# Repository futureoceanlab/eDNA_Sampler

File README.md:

# eDNA Sampler
This is a project that controls an autonomous eDNA Sampler. There are two modules: ESP8266 based hardware controller and a Django Web Application for interact with ESP8266 wirelessly.

The detailed documentation on architecture, how-to-build, apparatus and testing can be found in eDNA_sampler.pdf in this repository. Furthermore, the link to view the overleaf can be found [here](https://www.overleaf.com/read/nvktmdfzfmym). Please send an email to junsuj@mit.edu if you would like to edit the documentation. 

## Current Apparatus
Feb 2020: We currently have one full-system ready to be disassembled in the lab. We have four packs of batteries and three housings with connectors ready to be assemebled. We have 9 PCB boards and required components to be soldered on the PCB.

# Overview of this repository

## webapp: Web App for online deployment configuration / data retrieval
The program is run on a virtual environment, so install the virtualenv on the machine that will run the Web App.

```bash
pip3 install virtualenv
```

In case that the virtualenv is installed in a path that is not listed (i.e. virtualenv will complain saying that there is no such command), please add the following line to the end of ~/.profile 

```bash
PATH=$PATH:$HOME/.local/bin
```

in eDNA_Sampler/webapp, enter the following line in the terminal

```bash
virtualenv env
source env/bin/activate
``` 

This should activate the virtual environment, and you are ready to install the required packages

```bash
pip3 install -r requirements.txt
```

The webserver hosts' IP address can be found at WLAN0 interface by running the following:

```bash
ifconfig
```

In the webapp directory, run the server

```bash
python3 manage.py runserver 0.0.0.0:5000
```

0.0.0.0 will listen to other devices connected through every interfaces. 5000 is the port, and it can be different as long as it does not coincide with other used ports. 

Finally, check the Firewall if the client cannot access the webapp.

## sampler_mcu: ESP8266 Based Arduino code
The system uses ESP8266 Huzzah from Adafruit and a variety of libraries, and thus, Arduino IDE requires some setup.

In particular, the libraries that need to be installed are:
[ESP8266](https://learn.adafruit.com/adafruit-huzzah-esp8266-breakout/using-arduino-ide), 
[GrooveNfc](https://github.com/Seeed-Studio/Seeed_Arduino_NFC), 
ArduinoJson,
[MS5837](https://github.com/bluerobotics/BlueRobotics_MS5837_Library), 
[TSYS01](https://github.com/bluerobotics/BlueRobotics_TSYS01_Library).

[ESP8266 Huzzah](https://learn.adafruit.com/adafruit-huzzah-esp8266-breakout/using-arduino-ide) explains how to program the device using FTDI converter.

## mechanical
This directory contains designs and schematics for mechanical components of the eDNA Sampler.
Specifically, we have 3D design of the battery housing and acrylic plates for the pvc clamp shell. 
There is also the electronics housing drawing for machining.

## pcb
This is the schematic and layout of the PCB design of the electronics.

## archive
This is a folder with ancient codes and files that were onced developed. They are irrelevant at this point, but archived in this folder.

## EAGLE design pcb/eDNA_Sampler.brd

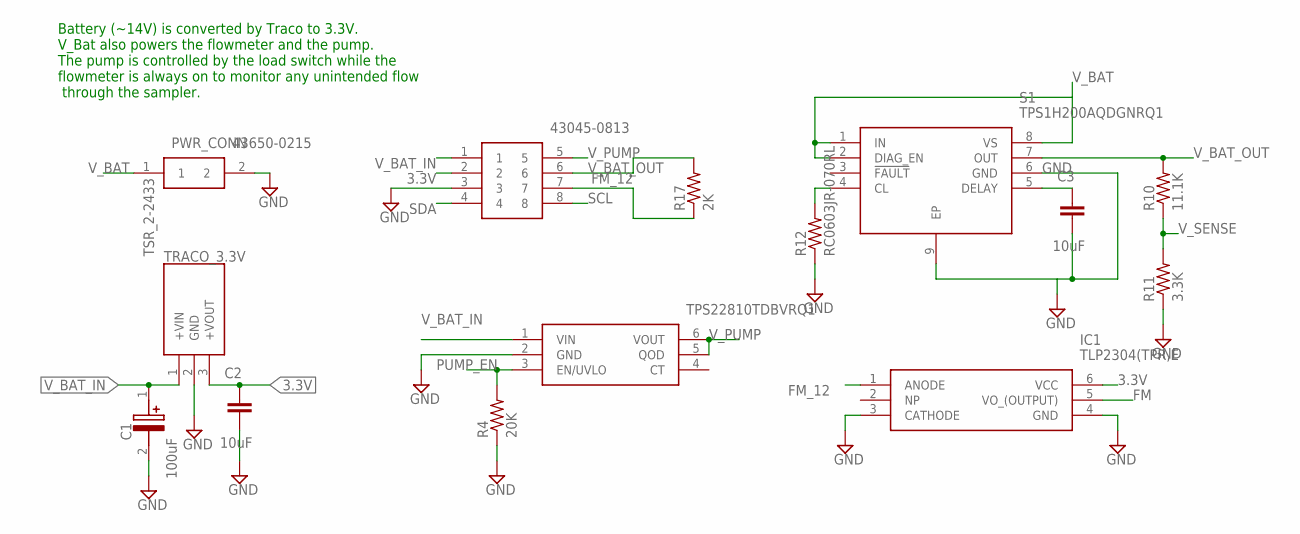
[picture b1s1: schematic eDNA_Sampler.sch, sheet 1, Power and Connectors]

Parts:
C1: 100uF; CAPPRD250W50D680H1250
C2, C3: 10uF; CAP_0603
IC1: TLP2304(TPR,E; SOIC127P700X230-6N
LOAD_SWITCH: TPS22810TDBVRQ1; SOT95P280X145-6N
PENETRATOR_CONN: 43045-0813
PWR_CONN: 43650-0215; 43650-0217
R4: 20K; RES_0603
R10: 11.1K; RES_0603
R11: 3.3K; RES_0603
R12: RC0603JR-070RL; RES_0603
R17: 2K; RES_0603
S1: TPS1H200AQDGNRQ1; SOP65P490X110-9N
TRACO_3.3V: TSR_2-2433; TSR-2

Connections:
3.3V: C2.1, IC1.6 (VCC), PENETRATOR_CONN.2, TRACO_3.3V.3 (+VOUT); also elsewhere on the board
FM: IC1.5 (VO_(OUTPUT)); also elsewhere on the board
FM_12: IC1.1 (ANODE), PENETRATOR_CONN.7, R17.1
GND: C1.2 (-), C2.2, C3.2, IC1.3 (CATHODE), IC1.4 (GND), LOAD_SWITCH.2 (GND), PENETRATOR_CONN.3, PWR_CONN.2, R4.1, R11.1, R12.1, S1.6 (GND), S1.9 (EP), TRACO_3.3V.2 (GND); also elsewhere on the board
unnamed: R12.2, S1.4 (CL)
unnamed: C3.1, S1.5 (DELAY)
PUMP_EN: LOAD_SWITCH.3 (EN/UVLO), R4.2; also elsewhere on the board
SCL: PENETRATOR_CONN.8; also elsewhere on the board
SDA: PENETRATOR_CONN.4; also elsewhere on the board
V_BAT: PWR_CONN.1, S1.1 (IN), S1.2 (DIAG_EN), S1.8 (VS)
V_BAT_IN: C1.1 (+), LOAD_SWITCH.1 (VIN), PENETRATOR_CONN.1, TRACO_3.3V.1 (+VIN)
V_BAT_OUT: PENETRATOR_CONN.6, R10.2, R17.2, S1.7 (OUT)
V_PUMP: LOAD_SWITCH.5 (QOD), LOAD_SWITCH.6 (VOUT), PENETRATOR_CONN.5
V_SENSE: R10.1, R11.2; also elsewhere on the board

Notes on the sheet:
Battery (~14V) is converted by Traco to 3.3V. V_Bat also powers the flowmeter and the pump. The pump is controlled by the load switch while the flowmeter is always on to monitor any unintended flow through the sampler.

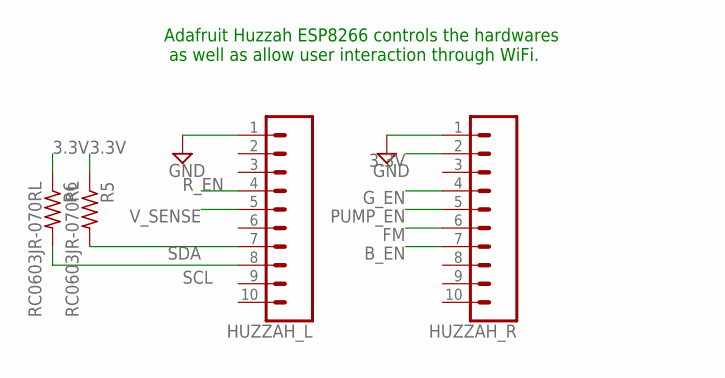
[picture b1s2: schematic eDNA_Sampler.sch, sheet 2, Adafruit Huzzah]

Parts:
HUZZAH_L: CONN_10"; 1X10
HUZZAH_R: CONN_10"; 1X10
R5, R6: RC0603JR-070RL; RES_0603

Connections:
3.3V: HUZZAH_R.2, R5.1, R6.1; also elsewhere on the board
B_EN: HUZZAH_R.7; also elsewhere on the board
FM: HUZZAH_R.6; also elsewhere on the board
GND: HUZZAH_L.1, HUZZAH_R.1; also elsewhere on the board
G_EN: HUZZAH_R.4; also elsewhere on the board
PUMP_EN: HUZZAH_R.5; also elsewhere on the board
R_EN: HUZZAH_L.4; also elsewhere on the board
SCL: HUZZAH_L.8, R6.2; also elsewhere on the board
SDA: HUZZAH_L.7, R5.2; also elsewhere on the board
V_SENSE: HUZZAH_L.5; also elsewhere on the board

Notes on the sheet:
Adafruit Huzzah ESP8266 controls the hardwares as well as allow user interaction through WiFi.

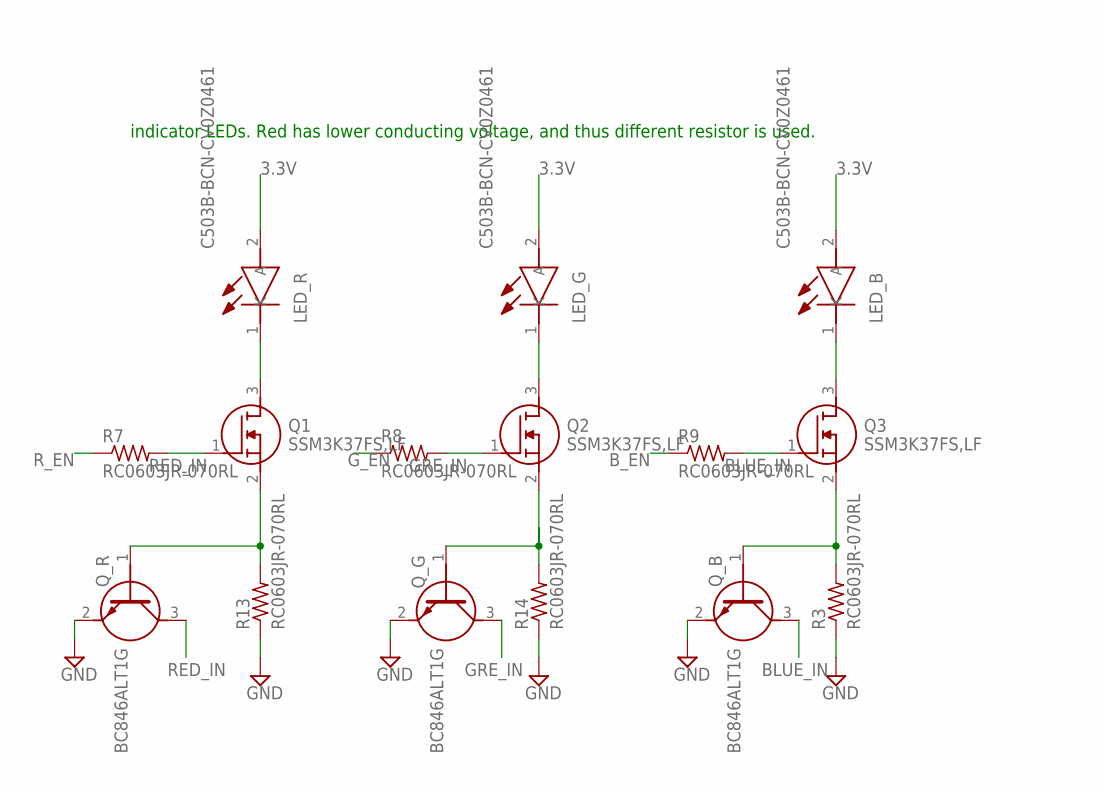
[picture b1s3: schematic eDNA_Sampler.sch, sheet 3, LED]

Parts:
LED_B: C503B-BCN-CV0Z0461; C503B-BCN
LED_G: C503B-BCN-CV0Z0461; C503B-BCN
LED_R: C503B-BCN-CV0Z0461; C503B-BCN
Q1, Q2, Q3: SSM3K37FS,LF; SSM3K37FSLF
Q_B: BC846ALT1G; SOT95P237X111-3N
Q_G: BC846ALT1G; SOT95P237X111-3N
Q_R: BC846ALT1G; SOT95P237X111-3N
R3, R7, R8, R9, R13, R14: RC0603JR-070RL; RES_0603

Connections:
3.3V: LED_B.2 (A), LED_G.2 (A), LED_R.2 (A); also elsewhere on the board
BLUE_IN: Q3.1 (G), Q_B.3 (C), R9.2
B_EN: R9.1; also elsewhere on the board
GND: Q_B.2 (E), Q_G.2 (E), Q_R.2 (E), R3.1, R13.1, R14.1; also elsewhere on the board
GRE_IN: Q2.1 (G), Q_G.3 (C), R8.2
G_EN: R8.1; also elsewhere on the board
unnamed: LED_R.1 (K), Q1.3 (D)
unnamed: LED_G.1 (K), Q2.3 (D)
unnamed: Q2.2 (S), Q_G.1 (B), R14.2
unnamed: Q1.2 (S), Q_R.1 (B), R13.2
unnamed: Q3.2 (S), Q_B.1 (B), R3.2
unnamed: LED_B.1 (K), Q3.3 (D)
RED_IN: Q1.1 (G), Q_R.3 (C), R7.2
R_EN: R7.1; also elsewhere on the board

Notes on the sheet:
indicator LEDs. Red has lower conducting voltage, and thus different resistor is used.

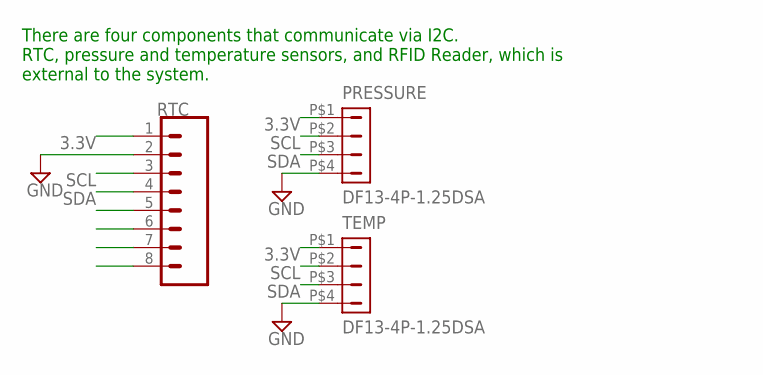
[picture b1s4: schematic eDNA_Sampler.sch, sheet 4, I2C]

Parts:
PRESSURE: DF13-4P-1.25DSA
RTC: CONN_08"; 1X08
TEMP: DF13-4P-1.25DSA

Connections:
3.3V: PRESSURE.P$1 (1), RTC.1, TEMP.P$1 (1); also elsewhere on the board
GND: PRESSURE.P$4 (4), RTC.2, TEMP.P$4 (4); also elsewhere on the board
SCL: PRESSURE.P$2 (2), RTC.3, TEMP.P$2 (2); also elsewhere on the board
SDA: PRESSURE.P$3 (3), RTC.4, TEMP.P$3 (3); also elsewhere on the board

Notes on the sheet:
There are four components that communicate via I2C. RTC, pressure and temperature sensors, and RFID Reader, which is external to the system.

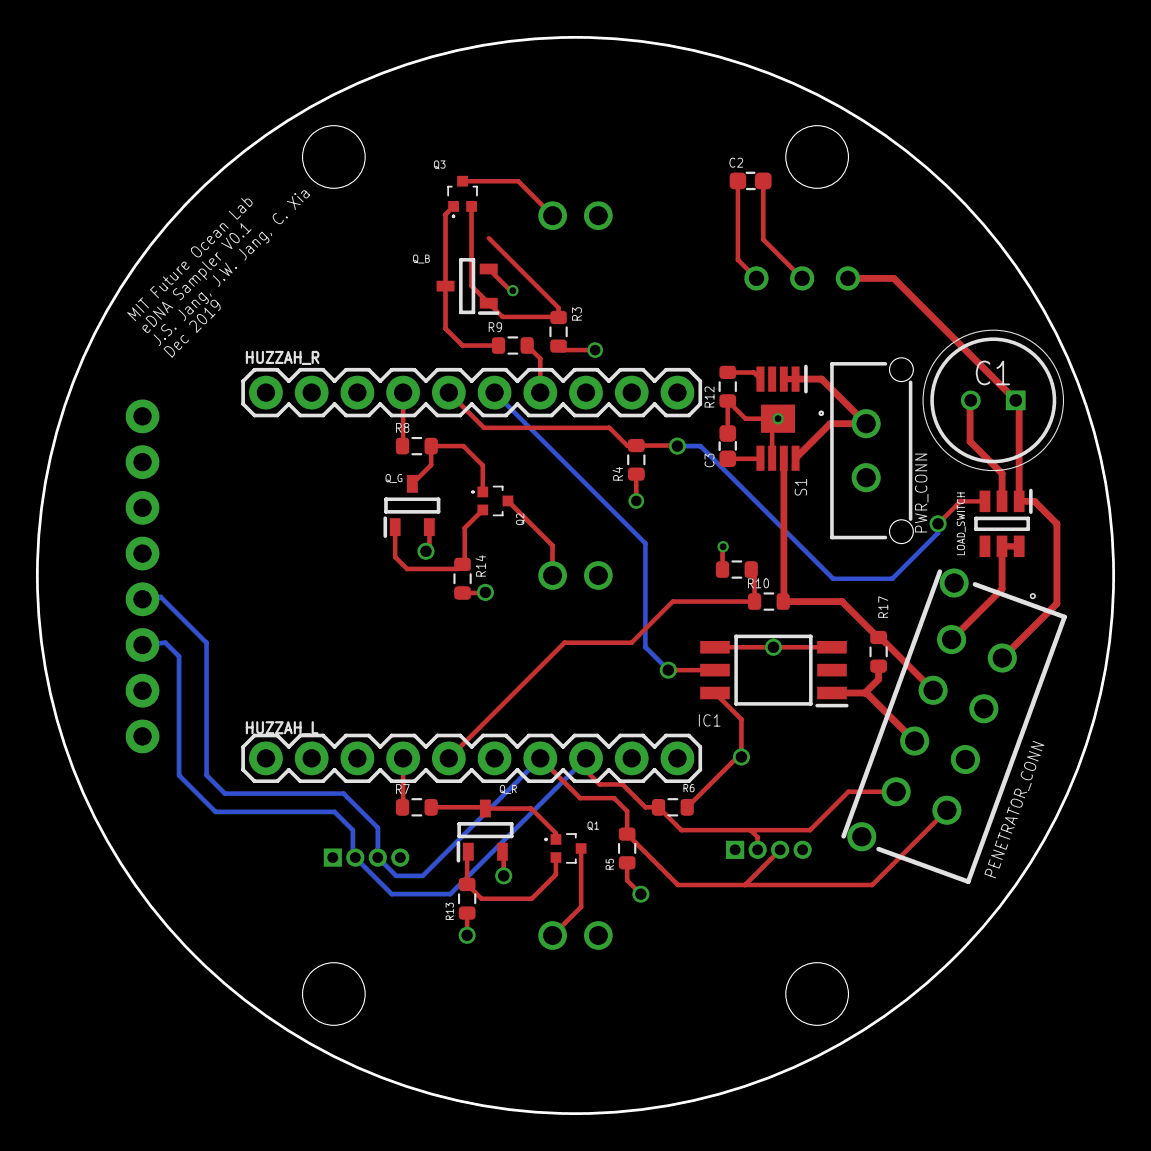
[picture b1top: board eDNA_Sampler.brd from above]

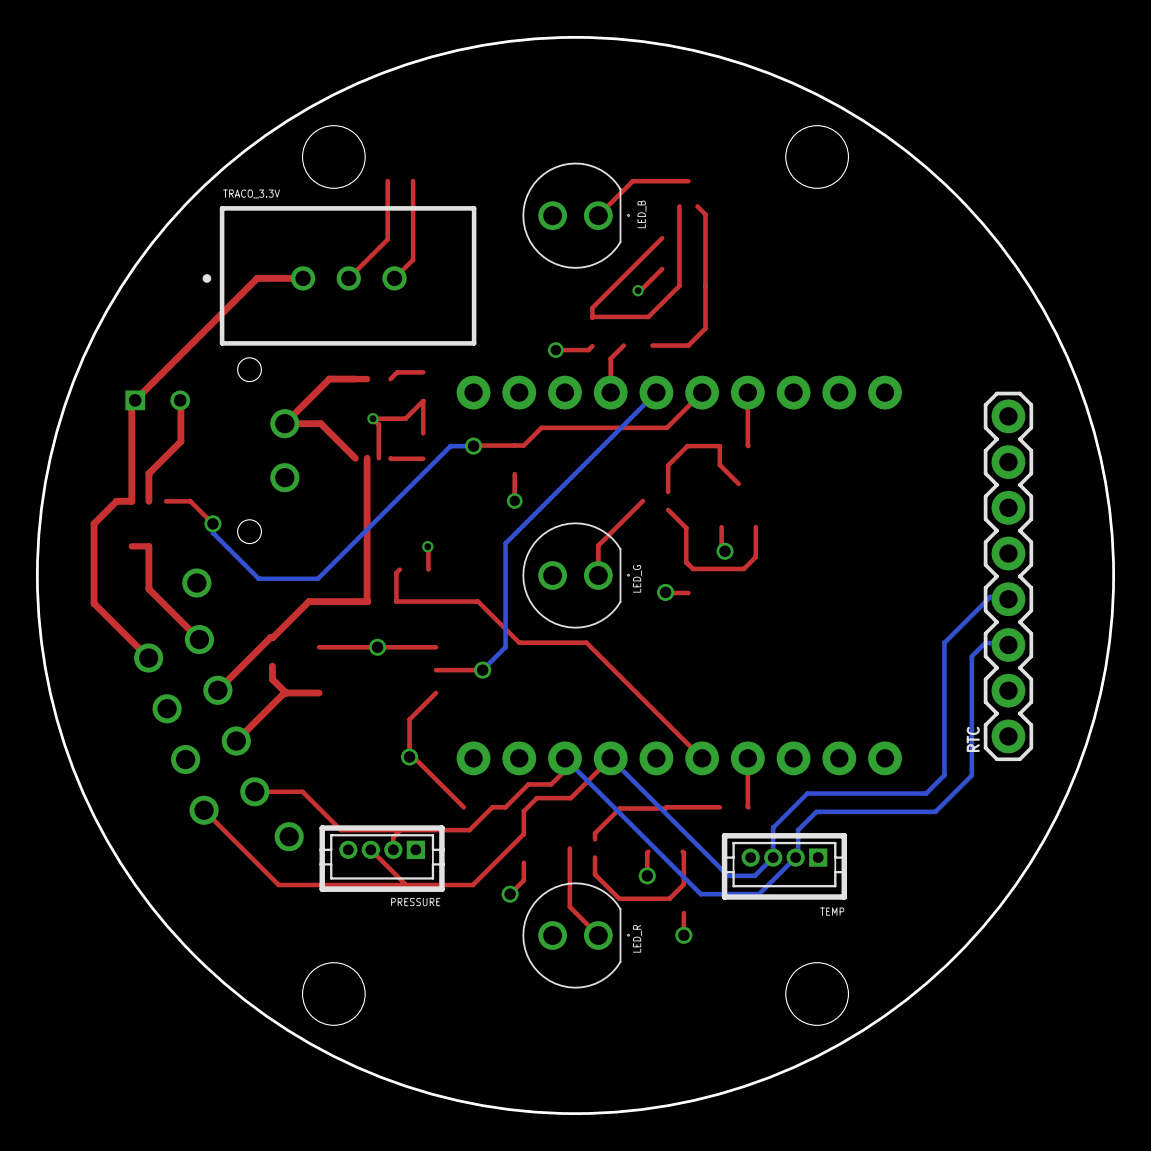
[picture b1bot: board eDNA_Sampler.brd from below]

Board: 4 copper layers, 59.8 x 59.8 mm, 36 parts (7 on the bottom side), 26 nets.

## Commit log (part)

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2019-11-05 add flowmeter tick conversion
2019-11-05 add a script that will automatically run the server with virtualenv
2019-11-06 uncomment the conditions on deployment
2019-11-06 add ifdef DEBUG clauses
2019-11-06 change the name of the file to match the directory name
2019-11-07 cater to the new loggistics where the RFID will be tagged and power cycled
2019-11-09 added library for kellerLP
2019-11-21 changes to satisfy the depth trigger
2019-11-30 changes to adapt more parameters
2019-11-30 modularize the conditionals
2019-12-02 log files and conditions update
2019-12-02 receives log file, checkes for invalid inputs
2019-12-03 incorrect formatted data file and log conditions
2019-12-03 added instruction for details page
2019-12-03 user manual added
2019-12-04 modified templates to work with smaller screens
2019-12-04 add non-empty log file
2019-12-04 update readme file
2019-12-07 add plot creation to webapp
2019-12-07 requirement update with matplot
2019-12-07 Bump django from 2.2.6 to 2.2.8 in /webapp
    Bumps [django](https://github.com/django/django) from 2.2.6 to 2.2.8.
    - [Release notes](https://github.com/django/django/releases)
    - [Commits](https://github.com/django/django/compare/2.2.6...2.2.8)
2019-12-08 hardcoded version
2020-01-14 update webapp fix with plots and offline code
2020-01-14 remove DS Store
2020-01-23 add battery, housing and pvc shell .step files as well as drawings
2020-01-23 add circuit schematics and layouts
2020-01-23 refactor the code into a sampler_mcu directory
2020-01-23 remove environment files
2020-01-23 remove eDNA_v0
2020-01-23 move offline code to archive
2020-01-23 remove DS store file
2020-01-23 add data and logs directory to webapp
2020-01-23 remove pycache in migrations
2020-01-23 added comments with details on each functions
2020-01-23 update the readme
2020-01-23 update django framework
2020-01-23 Bump twisted from 17.9.0 to 19.7.0 in /webapp
    Bumps [twisted](https://github.com/twisted/twisted) from 17.9.0 to 19.7.0.
    - [Release notes](https://github.com/twisted/twisted/releases)
    - [Changelog](https://github.com/twisted/twisted/blob/trunk/NEWS.rst)
    - [Commits](https://github.com/twisted/twisted/compare/twisted-17.9.0...twisted-19.7.0)
2020-01-23 Bump pyyaml from 3.12 to 5.1 in /webapp
    Bumps [pyyaml](https://github.com/yaml/pyyaml) from 3.12 to 5.1.
    - [Release notes](https://github.com/yaml/pyyaml/releases)
    - [Changelog](https://github.com/yaml/pyyaml/blob/master/CHANGES)
    - [Commits](https://github.com/yaml/pyyaml/compare/3.12...5.1)
2020-01-23 Bump cryptography from 2.1.4 to 2.3 in /webapp
    Bumps [cryptography](https://github.com/pyca/cryptography) from 2.1.4 to 2.3.
    - [Release notes](https://github.com/pyca/cryptography/releases)
    - [Changelog](https://github.com/pyca/cryptography/blob/master/CHANGELOG.rst)
    - [Commits](https://github.com/pyca/cryptography/compare/2.1.4...2.3)
2020-01-23 Bump requests from 2.18.4 to 2.20.0 in /webapp
    Bumps [requests](https://github.com/requests/requests) from 2.18.4 to 2.20.0.
    - [Release notes](https://github.com/requests/requests/releases)
    - [Changelog](https://github.com/psf/requests/blob/master/HISTORY.md)
    - [Commits](https://github.com/requests/requests/compare/v2.18.4...v2.20.0)
2020-01-23 Bump pyxdg from 0.25 to 0.26 in /webapp
    Bumps [pyxdg](https://github.com/takluyver/pyxdg) from 0.25 to 0.26.
    - [Release notes](https://github.com/takluyver/pyxdg/releases)
    - [Changelog](https://github.com/takluyver/pyxdg/blob/master/ChangeLog)
    - [Commits](https://github.com/takluyver/pyxdg/compare/rel-0.25...rel-0.26)
2020-01-23 updat outdated libraries
2020-01-27 move old manual to archive
2020-02-11 Bump django from 3.0.2 to 3.0.3 in /webapp
    Bumps [django](https://github.com/django/django) from 3.0.2 to 3.0.3.
    - [Release notes](https://github.com/django/django/releases)
    - [Commits](https://github.com/django/django/compare/3.0.2...3.0.3)
2020-02-14 add documentation
2020-02-14 update readme with documentation and current apparatus
2020-02-14 update files missing authors and their emails
2020-05-20 Bump httplib2 from 0.9.2 to 0.18.0 in /webapp
    Bumps [httplib2](https://github.com/httplib2/httplib2) from 0.9.2 to 0.18.0.
    - [Release notes](https://github.com/httplib2/httplib2/releases)
    - [Changelog](https://github.com/httplib2/httplib2/blob/master/CHANGELOG)
    - [Commits](https://github.com/httplib2/httplib2/compare/0.9.2...v0.18.0)
2020-10-27 Bump cryptography from 2.8 to 3.2 in /webapp
    Bumps [cryptography](https://github.com/pyca/cryptography) from 2.8 to 3.2.
    - [Release notes](https://github.com/pyca/cryptography/releases)
    - [Changelog](https://github.com/pyca/cryptography/blob/master/CHANGELOG.rst)
    - [Commits](https://github.com/pyca/cryptography/compare/2.8...3.2)
2021-02-08 Bump httplib2 from 0.9.2 to 0.19.0 in /webapp
    Bumps [httplib2](https://github.com/httplib2/httplib2) from 0.9.2 to 0.19.0.
    - [Release notes](https://github.com/httplib2/httplib2/releases)
    - [Changelog](https://github.com/httplib2/httplib2/blob/master/CHANGELOG)
    - [Commits](https://github.com/httplib2/httplib2/compare/0.9.2...v0.19.0)
2021-03-18 Bump django from 3.0.2 to 3.1.6 in /webapp
    Bumps [django](https://github.com/django/django) from 3.0.2 to 3.1.6.
    - [Release notes](https://github.com/django/django/releases)
    - [Commits](https://github.com/django/django/compare/3.0.2...3.1.6)
2021-03-19 Bump pillow from 6.2.0 to 8.1.1 in /webapp
    Bumps [pillow](https://github.com/python-pillow/Pillow) from 6.2.0 to 8.1.1.
    - [Release notes](https://github.com/python-pillow/Pillow/releases)
    - [Changelog](https://github.com/python-pillow/Pillow/blob/master/CHANGES.rst)
    - [Commits](https://github.com/python-pillow/Pillow/compare/6.2.0...8.1.1)
2021-03-20 Bump jinja2 from 2.10.3 to 2.11.3 in /webapp
    Bumps [jinja2](https://github.com/pallets/jinja) from 2.10.3 to 2.11.3.
    - [Release notes](https://github.com/pallets/jinja/releases)
    - [Changelog](https://github.com/pallets/jinja/blob/master/CHANGES.rst)
    - [Commits](https://github.com/pallets/jinja/compare/2.10.3...2.11.3)
2021-03-25 Bump pyyaml from 5.3 to 5.4 in /webapp
    Bumps [pyyaml](https://github.com/yaml/pyyaml) from 5.3 to 5.4.
    - [Release notes](https://github.com/yaml/pyyaml/releases)
    - [Changelog](https://github.com/yaml/pyyaml/blob/master/CHANGES)
    - [Commits](https://github.com/yaml/pyyaml/compare/5.3...5.4)
2021-04-08 Bump django from 3.0.2 to 3.0.14 in /webapp
    Bumps [django](https://github.com/django/django) from 3.0.2 to 3.0.14.
    - [Release notes](https://github.com/django/django/releases)
    - [Commits](https://github.com/django/django/compare/3.0.2...3.0.14)
2021-06-02 Bump urllib3 from 1.25.8 to 1.26.5 in /webapp
    Bumps [urllib3](https://github.com/urllib3/urllib3) from 1.25.8 to 1.26.5.
    - [Release notes](https://github.com/urllib3/urllib3/releases)
    - [Changelog](https://github.com/urllib3/urllib3/blob/main/CHANGES.rst)
    - [Commits](https://github.com/urllib3/urllib3/compare/1.25.8...1.26.5)
    ---
    updated-dependencies:
2021-06-04 Bump django from 3.0.2 to 3.1.9 in /webapp
    Bumps [django](https://github.com/django/django) from 3.0.2 to 3.1.9.
    - [Release notes](https://github.com/django/django/releases)
    - [Commits](https://github.com/django/django/compare/3.0.2...3.1.9)
    ---
    updated-dependencies:
    - dependency-name: django
2021-06-08 Bump pillow from 6.2.0 to 8.2.0 in /webapp
    Bumps [pillow](https://github.com/python-pillow/Pillow) from 6.2.0 to 8.2.0.
    - [Release notes](https://github.com/python-pillow/Pillow/releases)
    - [Changelog](https://github.com/python-pillow/Pillow/blob/master/CHANGES.rst)
    - [Commits](https://github.com/python-pillow/Pillow/compare/6.2.0...8.2.0)
    ---
    updated-dependencies:
2021-06-10 Bump django from 3.0.2 to 3.1.12 in /webapp
    Bumps [django](https://github.com/django/django) from 3.0.2 to 3.1.12.
    - [Release notes](https://github.com/django/django/releases)
    - [Commits](https://github.com/django/django/compare/3.0.2...3.1.12)
    ---
    updated-dependencies:
    - dependency-name: django
2021-09-08 Bump pillow from 6.2.0 to 8.3.2 in /webapp
    Bumps [pillow](https://github.com/python-pillow/Pillow) from 6.2.0 to 8.3.2.
    - [Release notes](https://github.com/python-pillow/Pillow/releases)
    - [Changelog](https://github.com/python-pillow/Pillow/blob/master/CHANGES.rst)
    - [Commits](https://github.com/python-pillow/Pillow/compare/6.2.0...8.3.2)
    ---
    updated-dependencies:
2022-01-13 Bump pillow from 6.2.0 to 9.0.0 in /webapp
    Bumps [pillow](https://github.com/python-pillow/Pillow) from 6.2.0 to 9.0.0.
    - [Release notes](https://github.com/python-pillow/Pillow/releases)
    - [Changelog](https://github.com/python-pillow/Pillow/blob/main/CHANGES.rst)
    - [Commits](https://github.com/python-pillow/Pillow/compare/6.2.0...9.0.0)
    ---
    updated-dependencies:
2022-02-11 Bump twisted from 19.10.0 to 22.1.0 in /webapp
    Bumps [twisted](https://github.com/twisted/twisted) from 19.10.0 to 22.1.0.
    - [Release notes](https://github.com/twisted/twisted/releases)
    - [Changelog](https://github.com/twisted/twisted/blob/trunk/NEWS.rst)
    - [Commits](https://github.com/twisted/twisted/compare/twisted-19.10.0...twisted-22.1.0)
    ---
    updated-dependencies:
2022-03-12 Bump pillow from 6.2.0 to 9.0.1 in /webapp
    Bumps [pillow](https://github.com/python-pillow/Pillow) from 6.2.0 to 9.0.1.
    - [Release notes](https://github.com/python-pillow/Pillow/releases)
    - [Changelog](https://github.com/python-pillow/Pillow/blob/main/CHANGES.rst)
    - [Commits](https://github.com/python-pillow/Pillow/compare/6.2.0...9.0.1)
    ---
    updated-dependencies:
2022-04-06 Bump twisted from 19.10.0 to 22.2.0 in /webapp
    Bumps [twisted](https://github.com/twisted/twisted) from 19.10.0 to 22.2.0.
    - [Release notes](https://github.com/twisted/twisted/releases)
    - [Changelog](https://github.com/twisted/twisted/blob/trunk/NEWS.rst)
    - [Commits](https://github.com/twisted/twisted/compare/twisted-19.10.0...twisted-22.2.0)
    ---
    updated-dependencies:
2022-05-25 Bump pyjwt from 1.5.3 to 2.4.0 in /webapp
    Bumps [pyjwt](https://github.com/jpadilla/pyjwt) from 1.5.3 to 2.4.0.
    - [Release notes](https://github.com/jpadilla/pyjwt/releases)
    - [Changelog](https://github.com/jpadilla/pyjwt/blob/master/CHANGELOG.rst)
    - [Commits](https://github.com/jpadilla/pyjwt/compare/1.5.3...2.4.0)
    ---
    updated-dependencies:
2022-05-26 Bump twisted from 19.10.0 to 22.4.0 in /webapp
    Bumps [twisted](https://github.com/twisted/twisted) from 19.10.0 to 22.4.0.
    - [Release notes](https://github.com/twisted/twisted/releases)
    - [Changelog](https://github.com/twisted/twisted/blob/trunk/NEWS.rst)
    - [Commits](https://github.com/twisted/twisted/compare/twisted-19.10.0...twisted-22.4.0)
    ---
    updated-dependencies:
2022-11-04 Bump twisted from 19.10.0 to 22.10.0 in /webapp
    Bumps [twisted](https://github.com/twisted/twisted) from 19.10.0 to 22.10.0.
    - [Release notes](https://github.com/twisted/twisted/releases)
    - [Changelog](https://github.com/twisted/twisted/blob/trunk/NEWS.rst)
    - [Commits](https://github.com/twisted/twisted/compare/twisted-19.10.0...twisted-22.10.0)
    ---
    updated-dependencies:
2022-11-22 Bump pillow from 6.2.0 to 9.3.0 in /webapp
    Bumps [pillow](https://github.com/python-pillow/Pillow) from 6.2.0 to 9.3.0.
    - [Release notes](https://github.com/python-pillow/Pillow/releases)
    - [Changelog](https://github.com/python-pillow/Pillow/blob/main/CHANGES.rst)
    - [Commits](https://github.com/python-pillow/Pillow/compare/6.2.0...9.3.0)
    ---
    updated-dependencies:

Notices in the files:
parts and their libraries:
SparkFun-Connectors: Licensing: Creative Commons ShareAlike 4.0 International - https://creativecommons.org/licenses/by-sa/4.0
